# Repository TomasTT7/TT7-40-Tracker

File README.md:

# TT7-40-Tracker
Eagle files and code for TT7-40 high altitude balloon tracker.

The board consists of an ATMEGA328P running at 4MHz, an RFM22B transmitter and a UBLOX MAX7-C GPS module.
The code transmits a telemetry string via RTTY. (434.301MHz, 100 baud, 500Hz shift, 2 stop bits, ASCII 7)

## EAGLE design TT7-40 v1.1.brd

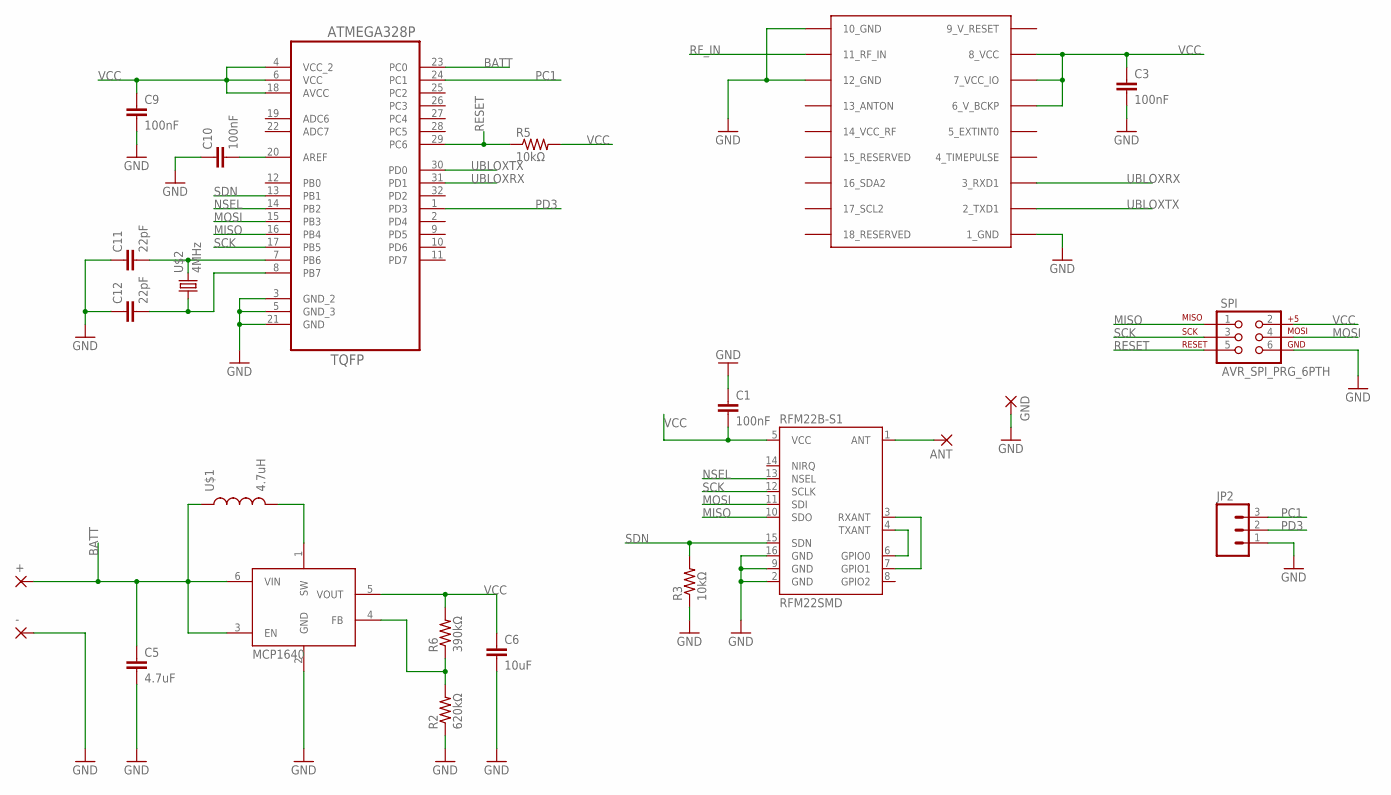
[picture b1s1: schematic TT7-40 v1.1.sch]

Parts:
+: WIREPADSMD1,27-254; SMD1,27-2,54
-: WIREPADSMD1,27-254; SMD1,27-2,54
ANT: WIREPADSMD1,27-254; SMD1,27-2,54
C1, C3, C9, C10: 100nF; 1206
C5: 4.7uF; 1206
C6: 10uF; 1206
C11, C12: 22pF; 0805
GND: WIREPADSMD1,27-254; SMD1,27-2,54
JP2: M03PTH; 1X03
R2: 620kΩ; 0805
R3, R5: 10kΩ; 0603-RES
R6: 390kΩ; 0805
RFM22B-S1: RFM22SMD; RFM22-XXX-S2
SPI: AVR_SPI_PRG_6PTH; 2X3
U2: MCP1640; SOT23-6
U3: ATMEGA328P-AU; QFP80P900X900X120-32N
U$1: 4.7uH; DER0705
U$2: 4MHz; ABM03_HC49
UBLOX-MAX7C: UBLOX_MAX

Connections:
9_V_RESET: UBLOX-MAX7C.9_V_RESET
BATT: +.1, C5.1, U2.3 (EN), U2.6 (VIN), U3.23 (PC0), U$1.P$1 (1)
GND: -.1, C1.1, C3.2, C5.2, C6.2, C9.2, C10.1, C11.1, C12.1, GND.1, JP2.1, R2.1, R3.1, RFM22B-S1.2 (GND), RFM22B-S1.9 (GND), RFM22B-S1.16 (GND), SPI.6, U2.2 (GND), U3.3 (GND_2), U3.5 (GND_3), U3.21 (GND), UBLOX-MAX7C.1_GND, UBLOX-MAX7C.10_GND, UBLOX-MAX7C.12_GND
MISO: RFM22B-S1.10 (SDO), SPI.1, U3.16 (PB4)
MOSI: RFM22B-S1.11 (SDI), SPI.4, U3.15 (PB3)
unnamed: RFM22B-S1.4 (TXANT), RFM22B-S1.6 (GPIO0)
unnamed: RFM22B-S1.3 (RXANT), RFM22B-S1.7 (GPIO1)
unnamed: ANT.1, RFM22B-S1.1 (ANT)
unnamed: U2.1 (SW), U$1.P$2 (2)
unnamed: C11.2, U3.7 (PB6), U$2.2
unnamed: R2.2, R6.1, U2.4 (FB)
unnamed: C12.2, U3.8 (PB7), U$2.1
unnamed: C10.2, U3.20 (AREF)
NSEL: RFM22B-S1.13 (NSEL), U3.14 (PB2)
PC1: JP2.3, U3.24 (PC1)
PD3: JP2.2, U3.1 (PD3)
RESET: R5.1, SPI.5, U3.29 (PC6)
RF_IN: UBLOX-MAX7C.11_RF_IN
SCK: RFM22B-S1.12 (SCLK), SPI.3, U3.17 (PB5)
SDN: R3.2, RFM22B-S1.15 (SDN), U3.13 (PB1)
UBLOXRX: U3.31 (PD1), UBLOX-MAX7C.3_RXD1
UBLOXTX: U3.30 (PD0), UBLOX-MAX7C.2_TXD1
VCC: C1.2, C3.1, C6.1, C9.1, R5.2, R6.2, RFM22B-S1.5 (VCC), SPI.2, U2.5 (VOUT), U3.4 (VCC_2), U3.6 (VCC), U3.18 (AVCC), UBLOX-MAX7C.6_V_BCKP, UBLOX-MAX7C.7_VCC_IO, UBLOX-MAX7C.8_VCC

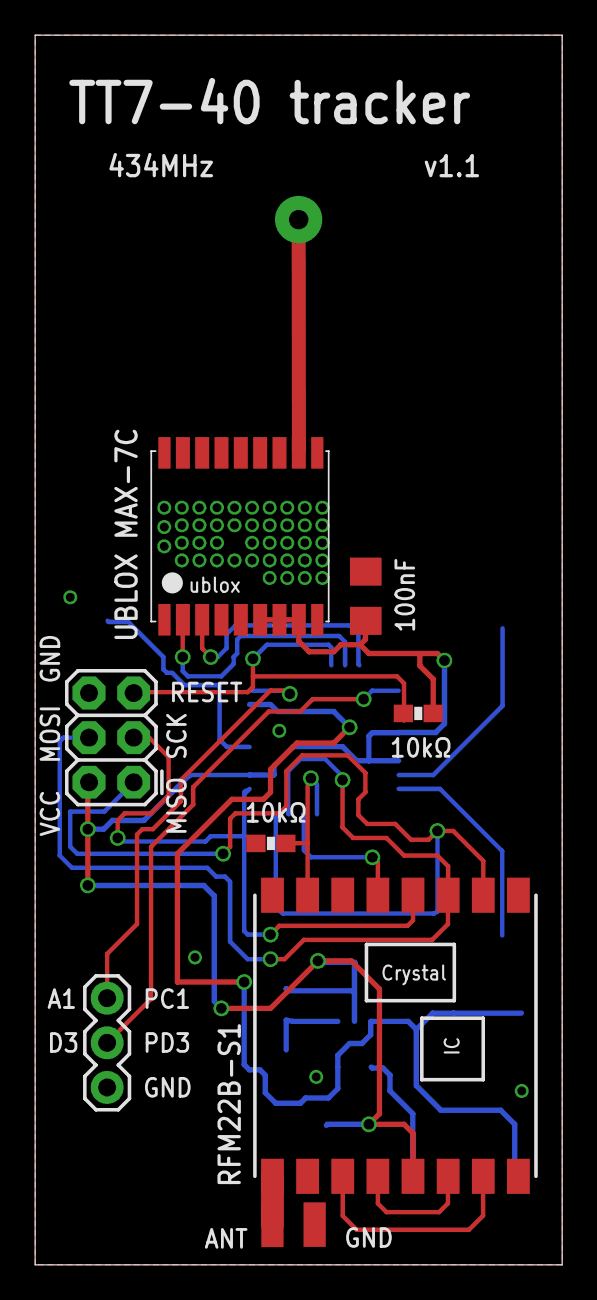
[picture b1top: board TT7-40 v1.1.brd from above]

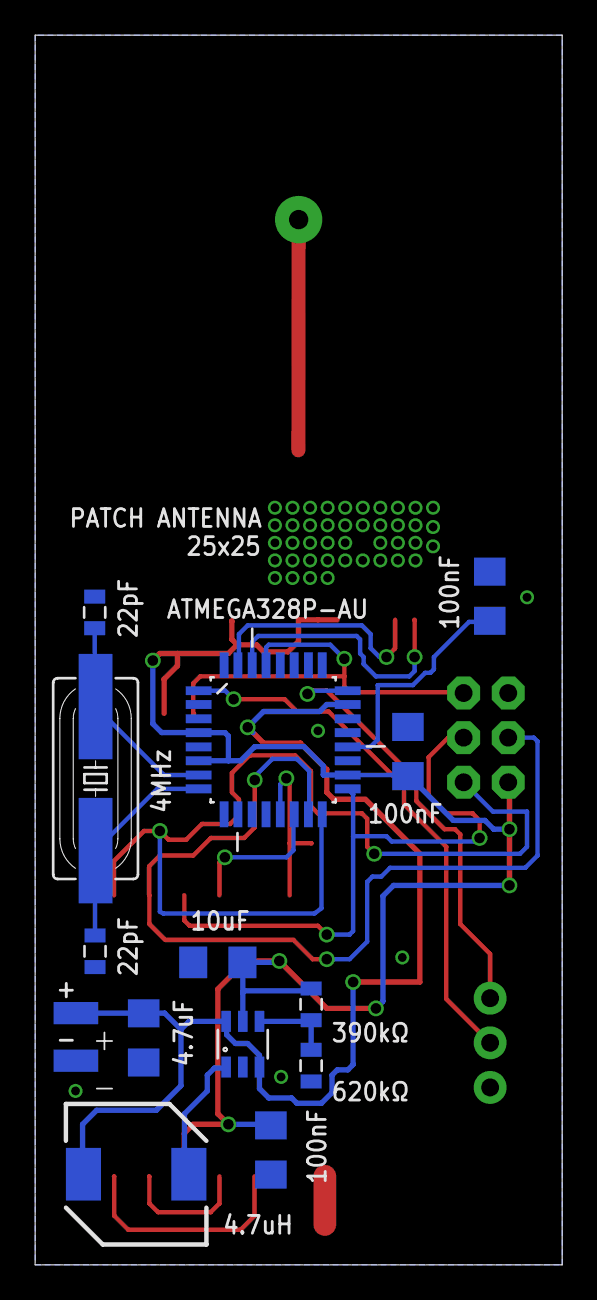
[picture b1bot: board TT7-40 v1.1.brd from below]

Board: 2 copper layers, 30.0 x 70.0 mm, 24 parts (15 on the bottom side), 21 nets.

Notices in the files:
parts and their libraries:
SparkFun-Capacitors: Licensing: Creative Commons ShareAlike 4.0 International - https://creativecommons.org/licenses/by-sa/4.0
